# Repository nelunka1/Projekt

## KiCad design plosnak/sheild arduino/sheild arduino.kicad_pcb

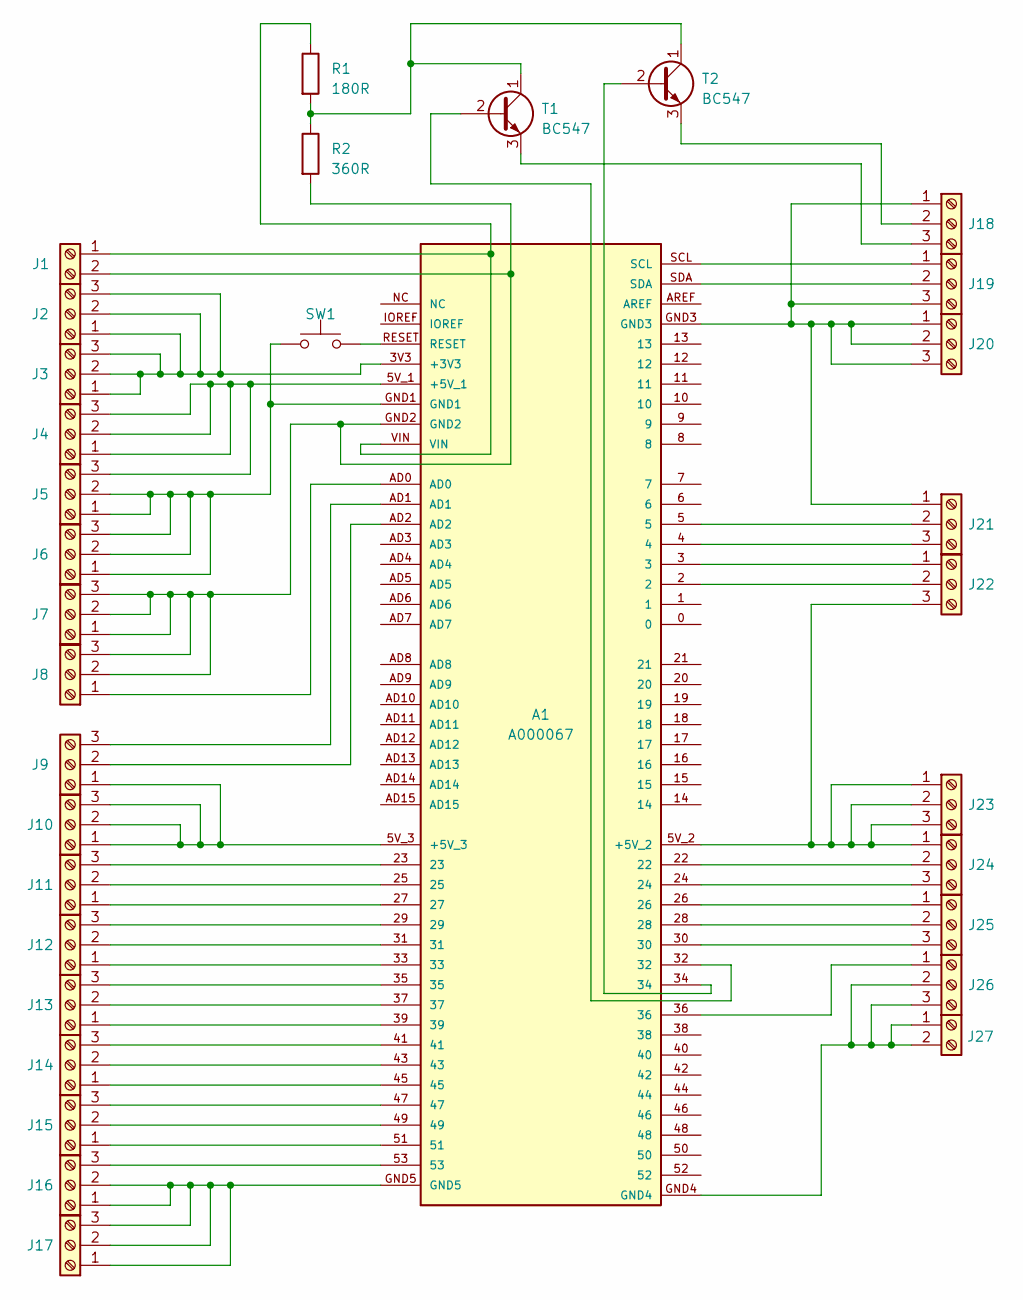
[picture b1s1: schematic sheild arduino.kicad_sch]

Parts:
A1: A000067; ARDUINO_A000067
J1: TerminalBlock_TE_282834-2_1x02_P2.54mm_Horizontal
J2, J3: 3,3V; TerminalBlock_TE_282834-3_1x03_P2.54mm_Horizontal
J4: 5V; TerminalBlock_TE_282834-3_1x03_P2.54mm_Horizontal
J5, J15, J20: GND; TerminalBlock_TE_282834-3_1x03_P2.54mm_Horizontal
J6: GND1; TerminalBlock_TE_282834-3_1x03_P2.54mm_Horizontal
J7: GND2; TerminalBlock_TE_282834-3_1x03_P2.54mm_Horizontal
J8: l; TerminalBlock_TE_282834-3_1x03_P2.54mm_Horizontal
J9: 5V3; TerminalBlock_TE_282834-3_1x03_P2.54mm_Horizontal
J10, J11, J12: Koleje; TerminalBlock_TE_282834-3_1x03_P2.54mm_Horizontal
J13, J14, J16, J17: Analog; TerminalBlock_TE_282834-3_1x03_P2.54mm_Horizontal
J18, J19: GND3; TerminalBlock_TE_282834-3_1x03_P2.54mm_Horizontal
J21, J23: Driver; TerminalBlock_TE_282834-3_1x03_P2.54mm_Horizontal
J22: 5V2; TerminalBlock_TE_282834-3_1x03_P2.54mm_Horizontal
J24: Tlacitka; TerminalBlock_TE_282834-3_1x03_P2.54mm_Horizontal
J25: +3; TerminalBlock_TE_282834-3_1x03_P2.54mm_Horizontal
J26: GND4; TerminalBlock_TE_282834-3_1x03_P2.54mm_Horizontal
J27: GND4; TerminalBlock_TE_282834-2_1x02_P2.54mm_Horizontal
R1: 180R; R_Axial_DIN0207_L6.3mm_D2.5mm_P10.16mm_Horizontal
R2: 360R; R_Axial_DIN0207_L6.3mm_D2.5mm_P10.16mm_Horizontal
SW1: SW_PUSH_6mm_H4.3mm
T1, T2: BC547; TO-92_Inline_Wide

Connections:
unnamed: A1.3V3 (+3V3), J2.1, J2.2, J2.3, J3.1, J3.2, J3.3
unnamed: A1.5V_1 (+5V_1), J4.1, J4.2, J4.3, J5.3
unnamed: A1.5V_2 (+5V_2), J22.3, J23.1, J23.2, J23.3, J24.1
unnamed: A1.5V_3 (+5V_3), J9.1, J10.1, J10.2, J10.3
unnamed: A1.RESET, SW1.2
unnamed: A1.VIN, J1.1, R1.1
unnamed: A1.GND2, J1.2, J7.1, J7.2, J7.3, J8.2, J8.3, R2.2
unnamed: A1.GND1, J5.1, J5.2, J6.1, J6.2, J6.3, SW1.1
unnamed: A1.AD0, J8.1
unnamed: A1.AD2, J9.2
unnamed: A1.AD1, J9.3
unnamed: A1.27, J11.1
unnamed: A1.25, J11.2
unnamed: A1.23, J11.3
unnamed: A1.33, J12.1
unnamed: A1.31, J12.2
unnamed: A1.29, J12.3
unnamed: A1.39, J13.1
unnamed: A1.37, J13.2
unnamed: A1.35, J13.3
unnamed: A1.45, J14.1
unnamed: A1.43, J14.2
unnamed: A1.41, J14.3
unnamed: A1.51, J15.1
unnamed: A1.49, J15.2
unnamed: A1.47, J15.3
unnamed: A1.GND5, J16.1, J16.2, J17.1, J17.2, J17.3
unnamed: A1.53, J16.3
unnamed: A1.GND3, J18.1, J19.3, J20.1, J20.2, J20.3, J21.1
unnamed: J18.2, T2.3 (E)
unnamed: J18.3, T1.3 (E)
unnamed: A1.SCL, J19.1
unnamed: A1.SDA, J19.2
unnamed: A1.5, J21.2
unnamed: A1.4, J21.3
unnamed: A1.3, J22.1
unnamed: A1.2, J22.2
unnamed: A1.22, J24.2
unnamed: A1.24, J24.3
unnamed: A1.26, J25.1
unnamed: A1.28, J25.2
unnamed: A1.30, J25.3
unnamed: A1.36, J26.1
unnamed: A1.GND4, J26.2, J26.3, J27.1, J27.2
unnamed: A1.32, T1.2 (B)
unnamed: R1.2, R2.1, T1.1 (C), T2.1 (C)
unnamed: A1.34, T2.2 (B)

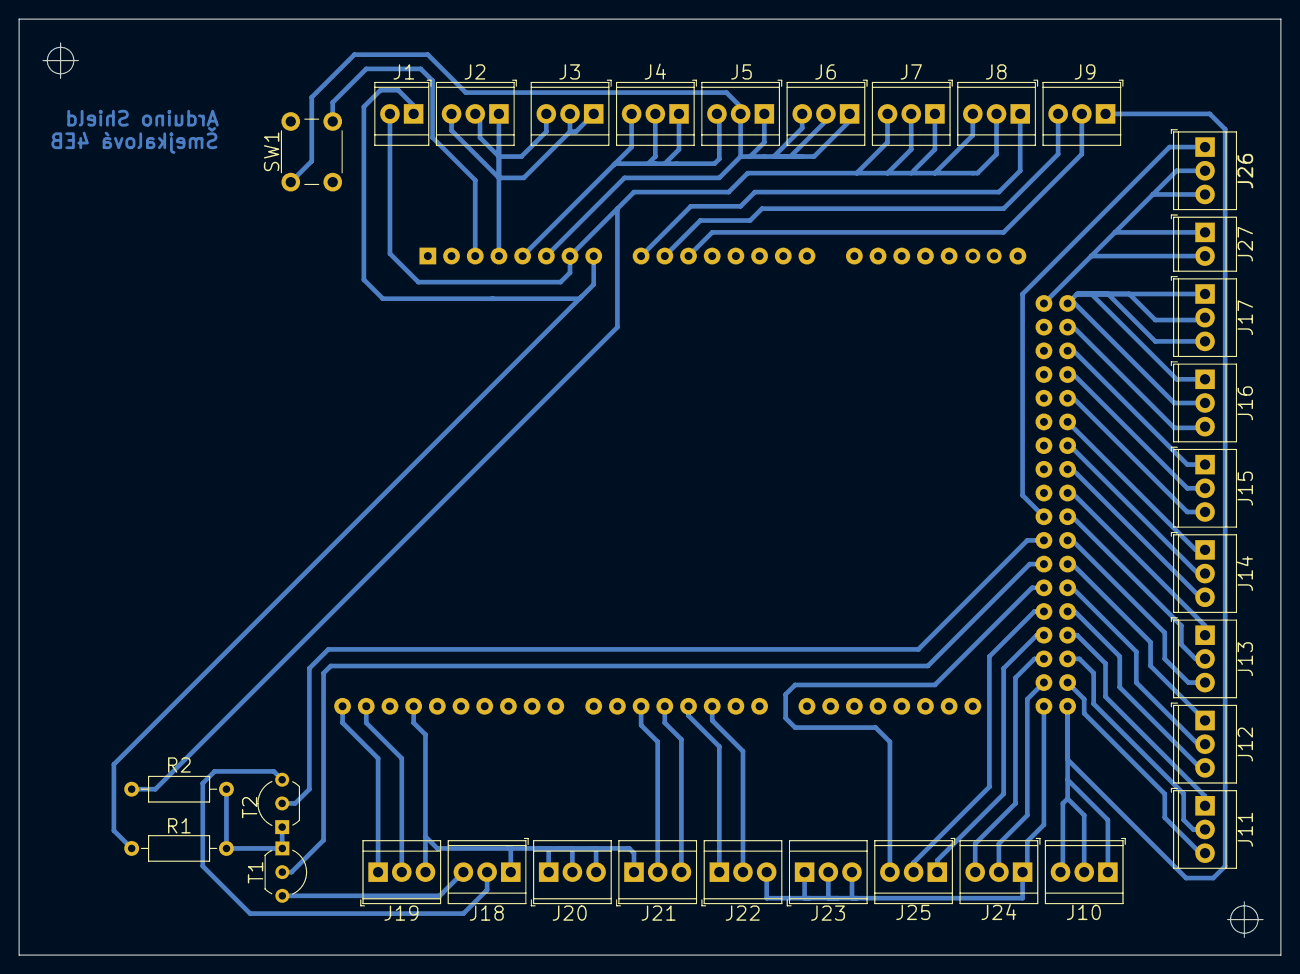
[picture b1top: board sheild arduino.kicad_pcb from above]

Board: 2 copper layers, 135.3 x 100.3 mm, 33 parts (1 on the bottom side), 47 nets.

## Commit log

2024-11-25 Přidání souborů
2024-12-08 novy
